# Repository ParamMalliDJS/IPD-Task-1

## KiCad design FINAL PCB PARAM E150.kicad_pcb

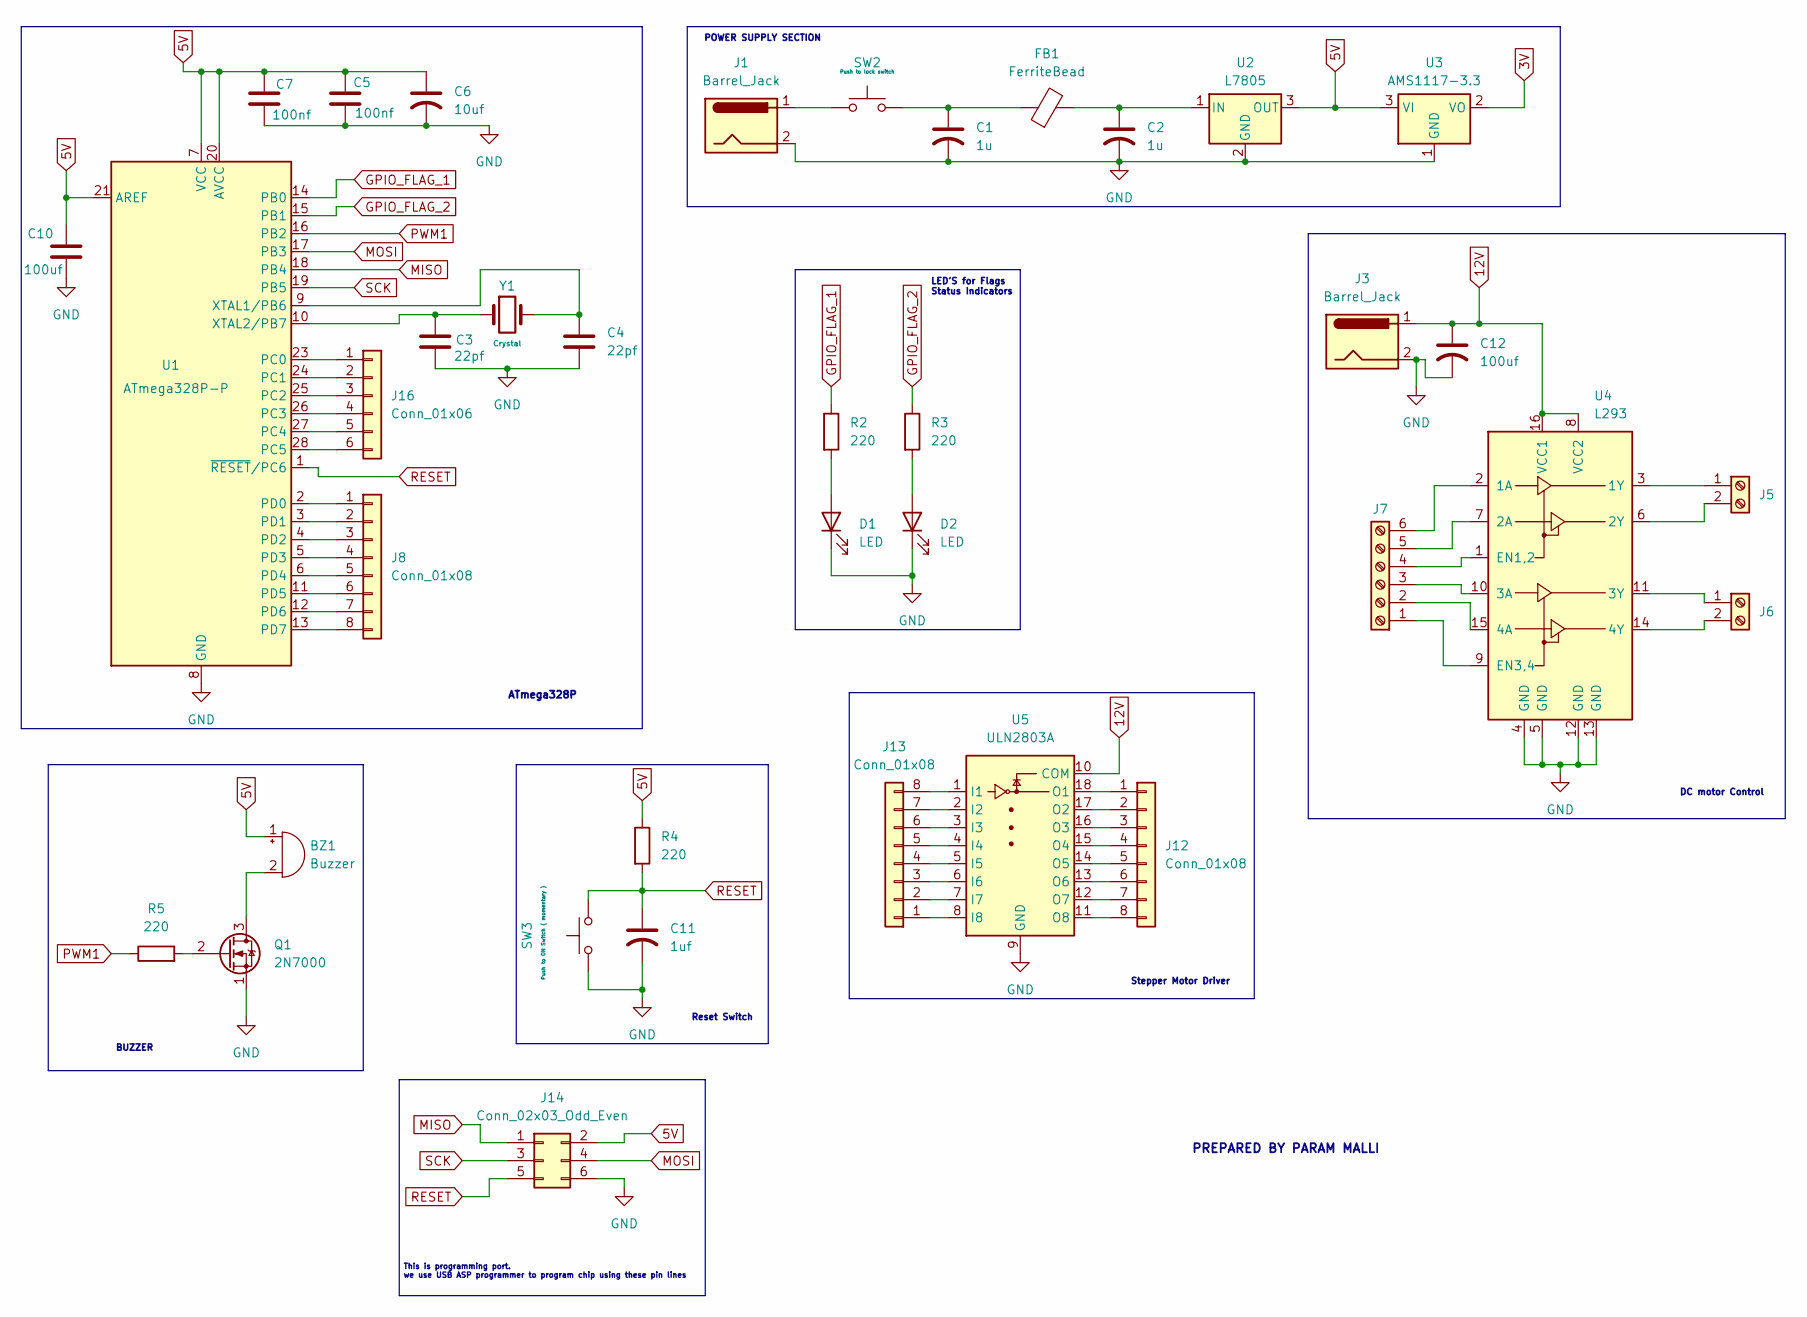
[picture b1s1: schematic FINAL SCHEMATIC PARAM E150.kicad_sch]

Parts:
BZ1: Buzzer; Buzzer_12x9.5RM7.6
C1, C2: 1u; CP_Radial_D5.0mm_P2.00mm
C3, C4: 22pf; C_Disc_D5.0mm_W2.5mm_P5.00mm
C5, C7: 100nf; C_Disc_D5.0mm_W2.5mm_P5.00mm
C6: 10uf; CP_Radial_D5.0mm_P2.00mm
C10: 100uf; CP_Radial_D8.0mm_P3.50mm
C11: 1uf; CP_Radial_D5.0mm_P2.00mm
C12: 100uf; CP_Radial_D5.0mm_P2.00mm
D1, D2: LED; LED_D5.0mm
FB1: FerriteBead; LairdTech_28C0236-0JW-10
J1, J3: Barrel_Jack; BarrelJack_Horizontal
J5, J6: Screw_Terminal_01x02; TerminalBlock_Phoenix_MKDS-1,5-2_1x02_P5.00mm_Horizontal
J7: Screw_Terminal_01x06; TerminalBlock_Phoenix_MKDS-1,5-6_1x06_P5.00mm_Horizontal
J8, J12, J13: Conn_01x08; PinHeader_1x08_P2.54mm_Vertical
J14: Conn_02x03_Odd_Even; PinHeader_2x03_P2.54mm_Vertical
J16: Conn_01x06; PinHeader_1x06_P2.54mm_Vertical
Q1: 2N7000; TO-92_Inline
R2, R3, R4, R5: 220; R_Axial_DIN0204_L3.6mm_D1.6mm_P7.62mm_Horizontal
SW2: Push to lock switch; SW_Slide_SPDT_Straight_CK_OS102011MS2Q
SW3: Push to ON Switch ( momentary ); SW_PUSH_6mm
U1: ATmega328P-P; DIP-28_W7.62mm
U2: L7805; TO-220-3_Vertical
U3: AMS1117-3.3; SOT-223-3_TabPin2
U4: L293; DIP-16_W7.62mm
U5: ULN2803A; DIP-18_W7.62mm
Y1: Crystal; Crystal_HC49-U_Vertical

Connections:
3V: U3.2 (VO)
5V: BZ1.1 (+), C5.1, C6.1, C7.1, C10.1, J14.2, R4.1, U1.7 (VCC), U1.20 (AVCC), U1.21 (AREF), U2.3 (OUT), U3.3 (VI)
12V: C12.1, J3.1, U4.8 (VCC2), U4.16 (VCC1), U5.10 (COM)
GND: C1.2, C2.2, C3.2, C4.2, C5.2, C6.2, C7.2, C10.2, C11.2, C12.2, D1.1 (K), D2.1 (K), J1.2, J3.2, J14.6, Q1.1 (S), SW3.1, U1.8 (GND), U1.22 (GND), U2.2 (GND), U3.1 (GND), U4.4 (GND), U4.5 (GND), U4.12 (GND), U4.13 (GND), U5.9 (GND)
GPIO_FLAG_1: R2.1, U1.14 (PB0)
GPIO_FLAG_2: R3.1, U1.15 (PB1)
MISO: J14.1, U1.18 (PB4)
MOSI: J14.4, U1.17 (PB3)
unnamed: BZ1.2 (-), Q1.3 (D)
unnamed: C1.1, FB1.1, SW2.2
unnamed: D1.2 (A), R2.2
unnamed: D2.2 (A), R3.2
unnamed: J1.1, SW2.1
unnamed: J5.1, U4.3 (1Y)
unnamed: J5.2, U4.6 (2Y)
unnamed: J6.1, U4.11 (3Y)
unnamed: J6.2, U4.14 (4Y)
unnamed: J7.1, U4.9 (EN3,4)
unnamed: J7.2, U4.15 (4A)
unnamed: J7.3, U4.10 (3A)
unnamed: J7.4, U4.1 (EN1,2)
unnamed: J7.5, U4.7 (2A)
unnamed: J7.6, U4.2 (1A)
unnamed: J8.1, U1.2 (PD0)
unnamed: J8.2, U1.3 (PD1)
unnamed: J8.3, U1.4 (PD2)
unnamed: J8.4, U1.5 (PD3)
unnamed: J8.5, U1.6 (PD4)
unnamed: J8.6, U1.11 (PD5)
unnamed: J8.7, U1.12 (PD6)
unnamed: J8.8, U1.13 (PD7)
unnamed: J12.1, U5.18 (O1)
unnamed: J12.2, U5.17 (O2)
unnamed: J12.3, U5.16 (O3)
unnamed: J12.4, U5.15 (O4)
unnamed: J12.5, U5.14 (O5)
unnamed: J12.6, U5.13 (O6)
unnamed: J12.7, U5.12 (O7)
unnamed: J12.8, U5.11 (O8)
unnamed: J13.1, U5.8 (I8)
unnamed: J13.2, U5.7 (I7)
unnamed: J13.3, U5.6 (I6)
unnamed: J13.4, U5.5 (I5)
unnamed: J13.5, U5.4 (I4)
unnamed: J13.6, U5.3 (I3)
unnamed: J13.7, U5.2 (I2)
unnamed: J13.8, U5.1 (I1)
unnamed: J16.1, U1.23 (PC0)
unnamed: J16.2, U1.24 (PC1)
unnamed: J16.3, U1.25 (PC2)
unnamed: J16.4, U1.26 (PC3)
unnamed: J16.5, U1.27 (PC4)
unnamed: J16.6, U1.28 (PC5)
unnamed: Q1.2 (G), R5.2
unnamed: C4.1, U1.9 (XTAL1/PB6), Y1.2
unnamed: C3.1, U1.10 (XTAL2/PB7), Y1.1
unnamed: C2.1, FB1.2, U2.1 (IN)
PWM1: R5.1, U1.16 (PB2)
RESET: C11.1, J14.5, R4.2, SW3.2, U1.1 (~RESET/PC6)
SCK: J14.3, U1.19 (PB5)

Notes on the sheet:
LED'S for Flags Status Indicators
BUZZER
Reset Switch
This is programming port. we use USB ASP programmer to program chip using these pin lines
Stepper Motor Driver
PREPARED BY PARAM MALLI
ATmega328P
DC motor Control
POWER SUPPLY SECTION

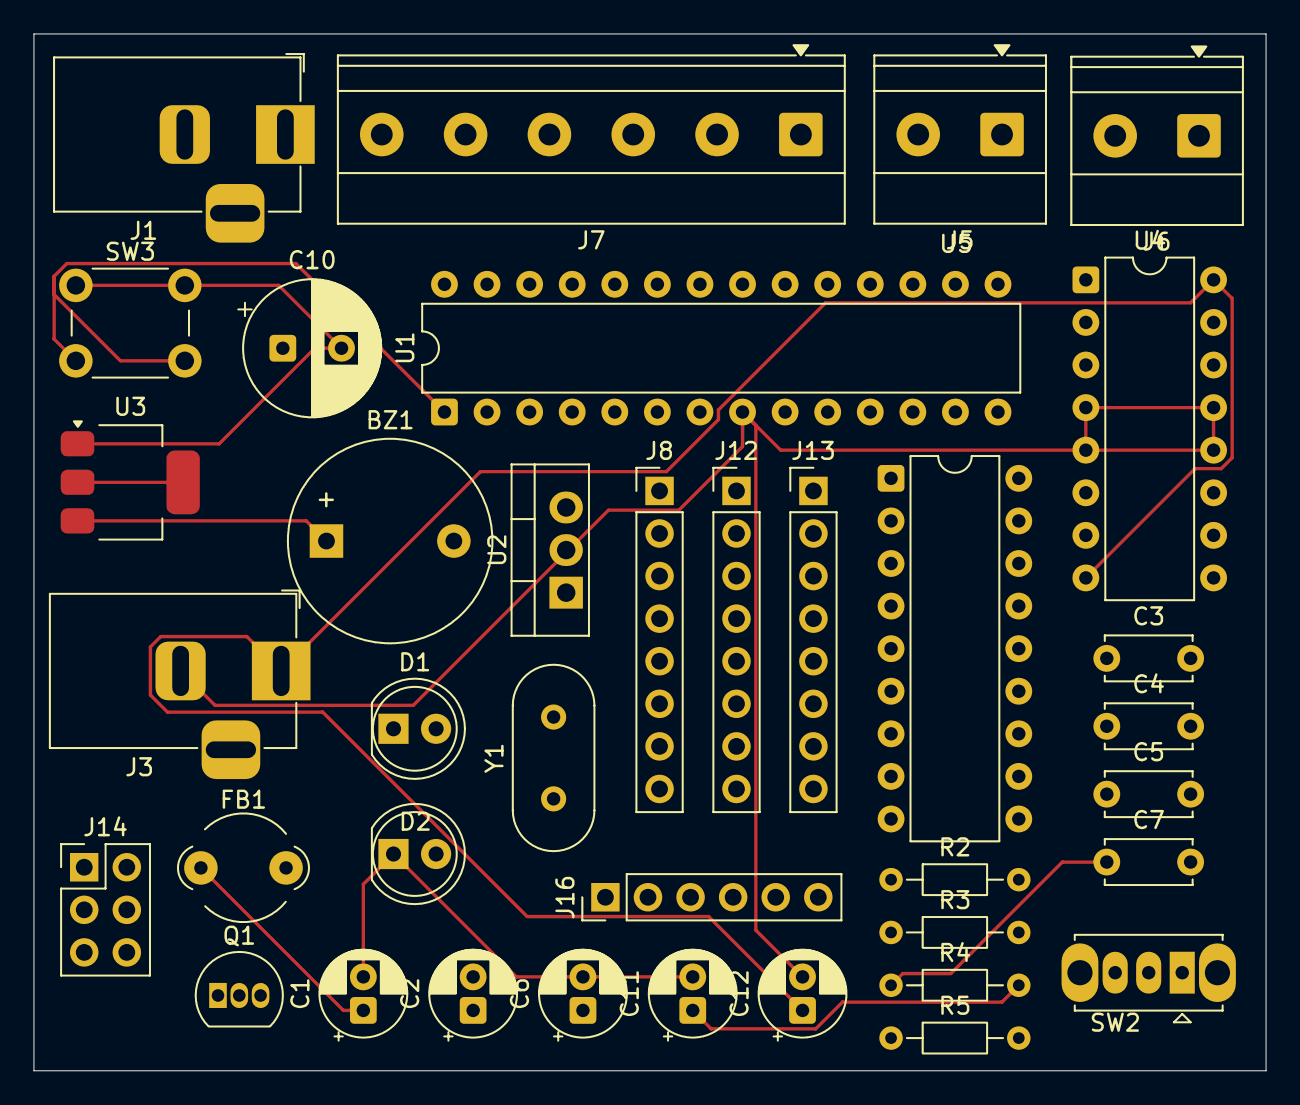
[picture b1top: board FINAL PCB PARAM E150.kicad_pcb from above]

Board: 14 copper layers, 73.5 x 61.8 mm, 37 parts (0 on the bottom side), 59 nets.

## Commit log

2026-03-13 Delete Screenshot 2026-03-13 231035.png
    delete
2026-03-13 Delete Screenshot 2026-03-13 231215.png
    delete
2026-03-13 Delete FINAL PCB PARAM E150.kicad_pro
    delete
2026-03-13 Delete FINAL SCHEMATIC PARAM E150.kicad_pro
    delete
